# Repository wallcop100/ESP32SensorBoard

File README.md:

# ESP32SensorBoard
ESP32 Sensor Board project: ESP32 Sensor Board  Welcome to the ESP32 Sensor Board repository! This project is a comprehensive solution for integrating various sensors with the ESP32 microcontroller. The board is designed to simplify the development of IoT applications, offering an easy way to connect and manage multiple sensors.

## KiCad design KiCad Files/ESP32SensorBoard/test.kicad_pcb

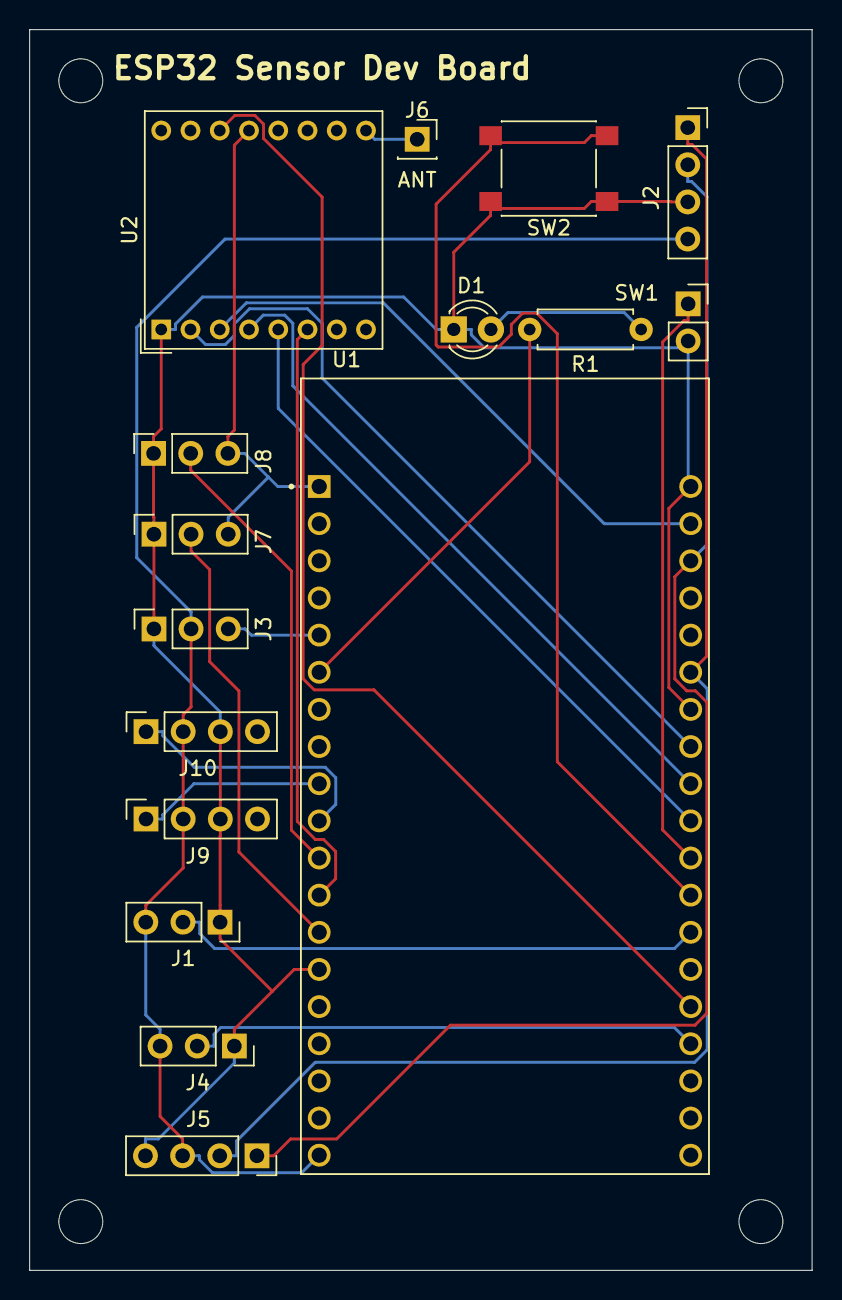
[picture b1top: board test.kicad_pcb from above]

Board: 2 copper layers, 53.5 x 84.8 mm, 16 parts (0 on the bottom side), 23 nets.

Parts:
D1: LED; LED_D3.0mm
J1, J4: 5V Sensor Header; PinSocket_1x03_P2.54mm_Vertical
J2, J5: I2C Header; PinSocket_1x04_P2.54mm_Vertical
J3: Servo Motor Header; PinSocket_1x03_P2.54mm_Vertical
J6: ANT; PinSocket_1x01_P2.54mm_Vertical
J7, J8: 3.3V Sensor Header; PinSocket_1x03_P2.54mm_Vertical
J9, J10: 5V Sensor Header; PinSocket_1x04_P2.54mm_Vertical
R1: R145; R_Axial_DIN0207_L6.3mm_D2.5mm_P7.62mm_Horizontal
SW1: SW_Push_Open; PinSocket_1x02_P2.54mm_Vertical
SW2: SW_Push_Open_Dual; SW_SPST_PTS645
U1: ESP32-DEVKITC-32D; MODULE_ESP32-DEVKITC-32D
U2: RFM95W-868S2; HOPERF_RFM9XW_THT

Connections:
+3.3V: J7.3, J8.3, U1.J2-1 (3V3), U2.13 (3.3V)
+5V: J1.3, J2.4, J3.2, J4.3, J5.3, J9.2, J10.2, U1.J2-19 (EXT_5V)
/IO4: J1.2, U1.J3-13 (IO4)
/IO12: J7.2, U1.J2-13 (IO12)
/IO15: J4.2, U1.J3-16 (IO15)
/IO25: J9.1, U1.J2-9 (IO25)
/IO26: J10.1, U1.J2-10 (IO26)
/IO27: J8.2, U1.J2-11 (IO27)
/IO34: J3.3, U1.J2-5 (IO34)
/SCL: J2.2, J5.1, U1.J3-3 (IO22)
/SDA: J2.1, J5.2, U1.J3-6 (IO21)
GND: D1.1 (K), J1.1, J2.3, J3.1, J4.1, J5.4, J7.1, J8.1, J9.3, J10.3, SW1.2 (B), SW2.1, U1.J2-14 (GND1), U1.J3-1 (GND3), U1.J3-7 (GND2), U2.1 (GND)
unnamed: D1.2 (A), R1.1
unnamed: J6.1, U2.9 (ANT)
unnamed: SW1.1 (A), U1.J3-11 (IO17)
unnamed: U1.J3-15 (IO2), U2.14 (DIO0)
unnamed: U1.J3-10 (IO5), U2.5 (NSS)
unnamed: U1.J2-12 (IO14), U2.6 (RESET)
unnamed: SW2.2, U1.J3-12 (IO16)
unnamed: U1.J3-9 (IO18), U2.4 (SCK)
unnamed: U1.J3-8 (IO19), U2.2 (MISO)
unnamed: U1.J3-2 (IO23), U2.3 (MOSI)
unnamed: R1.2, U1.J2-6 (IO35)

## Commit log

2024-05-16 Added PCB design files, schematic, BOM, and Gerber files
    This initial commit includes the essential hardware design files for the ESP32 Sensor Board project.
    Added files:
    - PCB Layout: Added PCB layout design files in SVG format for easy viewing and sharing.
    - Schematic: Added the complete schematic design of the ESP32 Sensor Board.
    These files provide a comprehensive overview of the hardware design and layout of the ESP32 Sensor Board, including multiple I2C headers and a connector for a LoRa module. These design files are cruc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
    Future updates will include firmware code, documentation, and example projects to facilit
2024-05-17 Added KiCad Files
    Added KiCad Files at:
    >\KiCad Files
2024-05-17 Added Image for ReadMe
